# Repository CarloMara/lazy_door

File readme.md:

# Lazy Door

A simple smarthome automation power endpoint. It has two independent triacs driven power channels controlled by a ZCO detector.
The endpoint is powered from AC, via a ac/dc module, that it's easily available online. 
In mk1 contains stuff for a prototype based on the linkit 7697 platform, which features an arm m4. Folder mk2 instead features a the same power circuits, but it's based on an esp8266

---
# mk1

This version is based on the demoboard of the linkit 7697. 
As the board will be placed inside a derivation box, it was chosen to integrate a ac/dc brick into the design, as it would provide an effective way to remove battery dependence. It was briefly considered a discrete implementation of an ac/dc converter, but since this module it's going to be done on a very small small scale it was deemed not worth.

Inspiration for the power side was drawn from both the datasheets and several books. The circuit was not simulated in spice.

# mk2

This board shares the sames design principles as the mk1 version, with the only exception of the microcontroller, which was changed in favor of an esp8266, as it's more readily available.

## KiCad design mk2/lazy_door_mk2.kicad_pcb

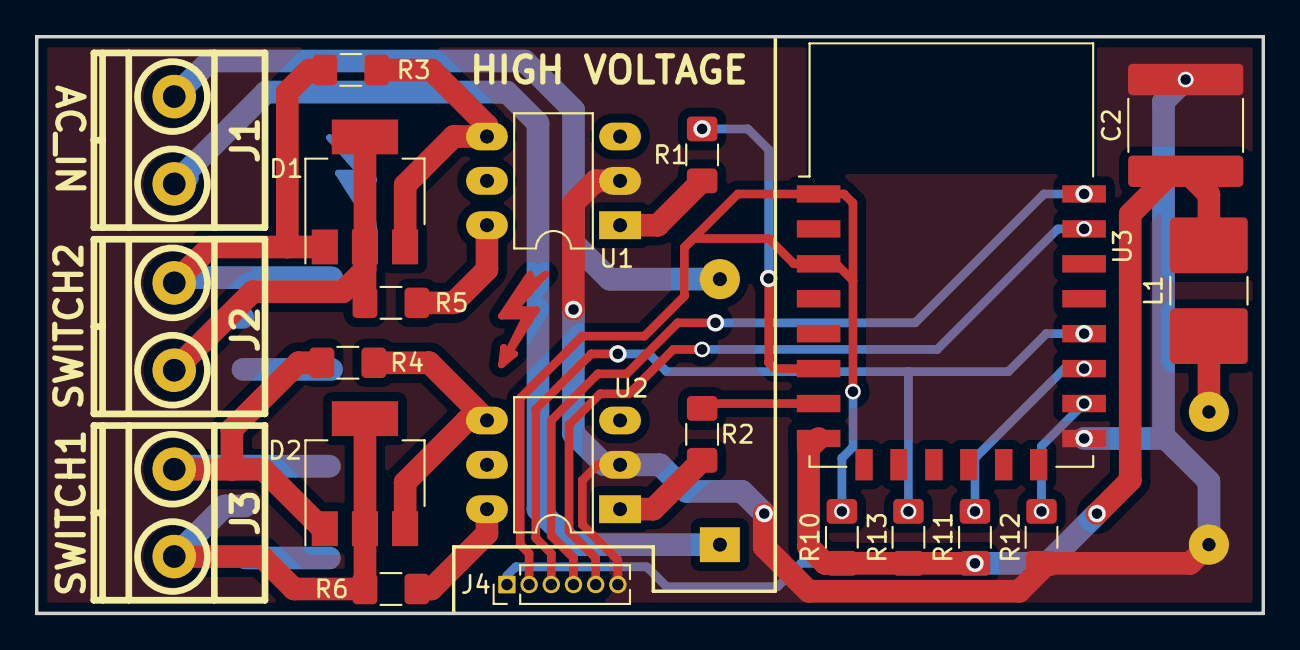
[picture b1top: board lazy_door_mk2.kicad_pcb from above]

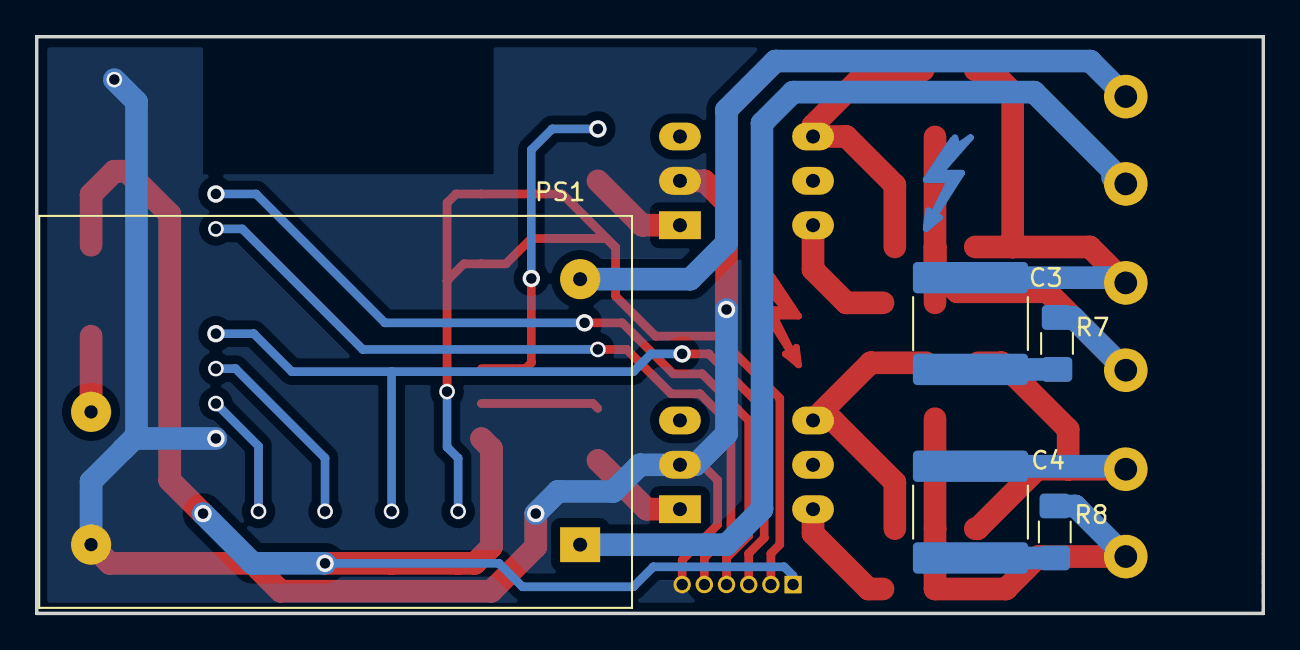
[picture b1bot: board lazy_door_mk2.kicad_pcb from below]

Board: 2 copper layers, 70.2 x 33.0 mm, 26 parts (5 on the bottom side), 25 nets.

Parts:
C2: C_Small; C_2225_5664Metric_Pad1.80x6.60mm_HandSolder
C3, C4: 0.1; C_2225_5664Metric_Pad1.80x6.60mm_HandSolder
D1, D2: Z0110MN; SOT-223
J1: AC_IN; mkds_1,5-2
J2: SWITCH2; mkds_1,5-2
J3: SWITCH1; mkds_1,5-2
J4: Conn_01x06_Female; PinHeader_1x06_P1.27mm_Vertical
L1: L_Small; L_2816_7142Metric_Pad3.20x4.45mm_HandSolder
PS1: IRM-02-3.3; Converter_ACDC_MeanWell_IRM-02-xx_THT
R1, R2: R; R_1206_3216Metric_Pad1.42x1.75mm_HandSolder
R3, R4: 330; R_1206_3216Metric_Pad1.42x1.75mm_HandSolder
R5, R6: 360; R_1206_3216Metric_Pad1.42x1.75mm_HandSolder
R7, R8: 39; R_1206_3216Metric_Pad1.42x1.75mm_HandSolder
R10, R11, R12: 3.3k; R_1206_3216Metric_Pad1.42x1.75mm_HandSolder
R13: 33k; R_1206_3216Metric_Pad1.42x1.75mm_HandSolder
U1, U2: MOC3042M; DIP-6_W7.62mm_LongPads
U3: ESP-12E

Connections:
+3V3: C2.1, J4.1, L1.2, R10.1, R11.1, R13.1, U3.8
/DTR: J4.3, R13.2, U3.18
/GPIO2: R11.2, U3.17
/GPIO15: R12.1, U3.16
/RTS: J4.2, R10.2, U3.1, U3.3
/RXD: J4.5, U3.21
/TXD: J4.4, U3.22
GND: C2.2, J4.6, PS1.3, R12.2, U1.2, U2.2, U3.15
unnamed: C3.1, R7.1
unnamed: C3.2, D1.1, J2.1, R3.1
unnamed: C4.1, R8.1
unnamed: C4.2, D2.1, J3.1, R4.1
unnamed: D1.2, D1.4, J2.2, R5.1, R7.2
unnamed: D1.3, R3.2, U1.4
unnamed: D2.2, D2.4, J3.2, R6.1, R8.2
unnamed: D2.3, R4.2, U2.4
unnamed: J1.1, PS1.2
unnamed: J1.2, PS1.1
unnamed: L1.1, PS1.4
unnamed: R1.1, U1.1
unnamed: R2.1, U2.1
unnamed: R5.2, U1.6
unnamed: R6.2, U2.6
SWITCH_1: R2.2, U3.7
SWITCH_2: R1.2, U3.6

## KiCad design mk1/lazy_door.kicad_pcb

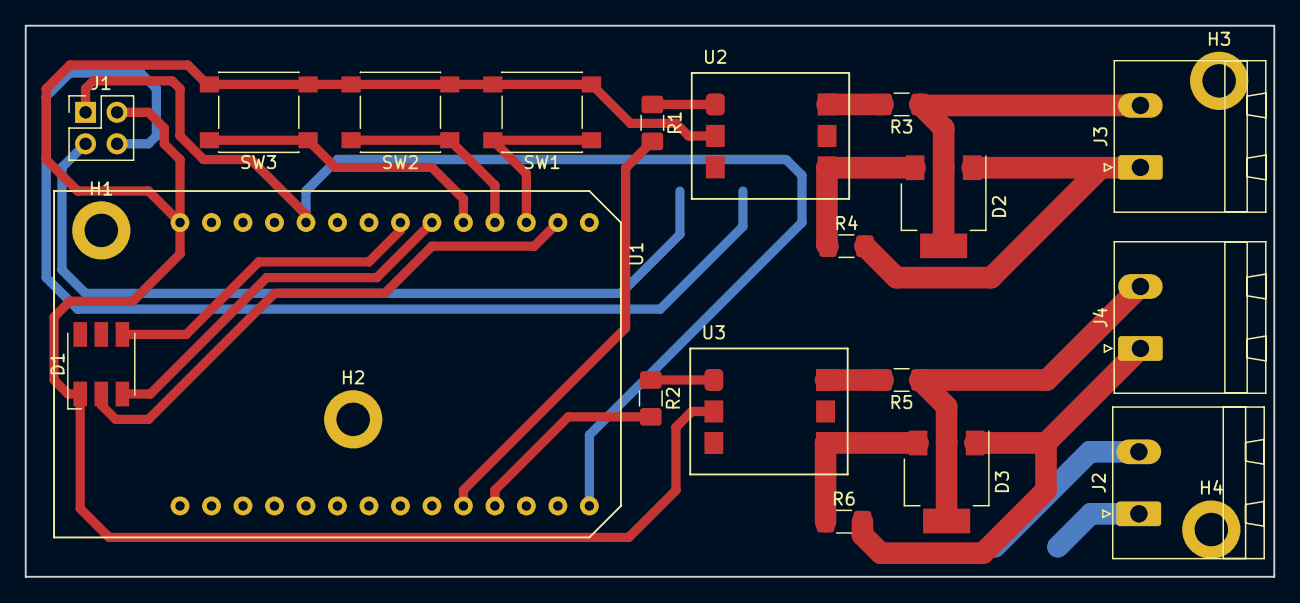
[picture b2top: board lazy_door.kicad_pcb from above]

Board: 2 copper layers, 100.7 x 44.5 mm, 24 parts (1 on the bottom side), 24 nets.

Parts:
D1: LED_CRGB; LED_RGB_5050-6
D2, D3: Z0110MN; SOT-223
H1, H2, H3, H4: MountingHole; MountingHole_2.7mm_M2.5_DIN965_Pad
J1: AC_POWER_SELECTOR; PinHeader_2x02_P2.54mm_Vertical
J2: AC_IN; PhoenixContact_MSTBA_2,5_2-G_1x02_P5.00mm_Horizontal
J3: HP_1_LOAD; PhoenixContact_MSTBA_2,5_2-G_1x02_P5.00mm_Horizontal
J4: HP_2_LOAD; PhoenixContact_MSTBA_2,5_2-G_1x02_P5.00mm_Horizontal
PS1: IRM-03-3.3S; Converter_ACDC_MeanWell_IRM-03-xx_SMD
R1: HP_1_BIAS; R_1206_3216Metric_Pad1.42x1.75mm_HandSolder
R2: HP_2_BIAS; R_1206_3216Metric_Pad1.42x1.75mm_HandSolder
R3, R5: 360; R_1206_3216Metric_Pad1.42x1.75mm_HandSolder
R4, R6: 330; R_1206_3216Metric_Pad1.42x1.75mm_HandSolder
SW1: EINT_2; SW_SPST_PTS645
SW2: EINT_0; SW_SPST_PTS645
SW3: EINT_22; SW_SPST_PTS645
U1: linkit7697; LINKIT_7697
U2, U3: MOC3042M

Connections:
+3V3: J1.1, U1.14, U1.24
/EINT0: SW2.1, U1.18
/EINT2: SW1.1, U1.17
/EINT22: SW3.1, U1.19
/LED_B: D1.4, U1.21
/LED_G: D1.3, U1.20
/LED_R: D1.2, U1.16
GND: D1.1, J1.2, SW1.2, SW2.2, SW3.2, U1.28, U2.2, U3.2
unnamed: D2.1, J3.1, R4.2
unnamed: D3.1, J4.1, R6.2
unnamed: D2.2, D2.4, J3.2, R3.1
unnamed: D2.3, R4.1, U2.4
unnamed: D3.2, D3.4, J4.2, R5.1
unnamed: D3.3, R6.1, U3.4
unnamed: J1.3, PS1.14
unnamed: J1.4, PS1.16
unnamed: J2.1, PS1.1
unnamed: J2.2, PS1.3
unnamed: R1.1, U2.1
unnamed: R1.2, U1.10
unnamed: R2.1, U3.1
unnamed: R2.2, U1.11
unnamed: R3.2, U2.6
unnamed: R5.2, U3.6

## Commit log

2019-02-05 First commit, add mk1 and mk2 kicad files. Add .gitignore for kicad temp files.
2019-02-05 add revision date on schematic. add images
2019-02-05 add images in readme
2019-02-05 fix images
2019-02-05 add board views
2019-02-05 compact layout of power element
2019-02-05 more compact layout, with power components only on one side
2019-02-05 Create ground plane
2019-02-05 add new layout images and renders
